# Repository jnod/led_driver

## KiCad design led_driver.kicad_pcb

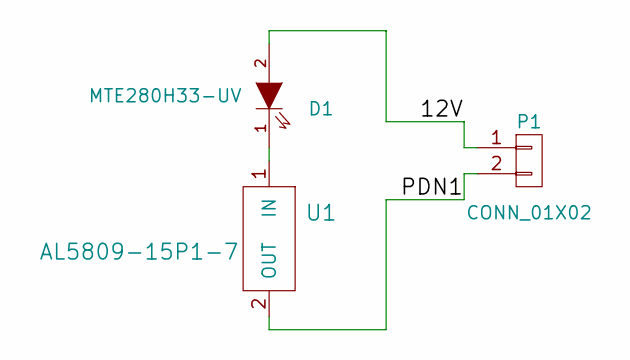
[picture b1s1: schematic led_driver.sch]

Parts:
D1: MTE280H33-UV; TO-5-2
P1: CONN_01X02; Sullins_M89_1X2
U1: AL5809-15P1-7; PowerDI-123_B

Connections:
/12V: D1.2 (A), P1.1
/PDN1: P1.2, U1.2 (OUT)
unnamed: D1.1 (K), U1.1 (IN)

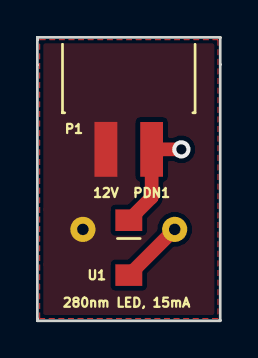
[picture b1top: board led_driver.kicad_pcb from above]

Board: 2 copper layers, 10.2 x 15.7 mm, 3 parts (1 on the bottom side), 3 nets.

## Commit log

2016-03-03 Add files to project
2016-03-04 Update silk screen
2016-03-06 Remove gerbers from repo
